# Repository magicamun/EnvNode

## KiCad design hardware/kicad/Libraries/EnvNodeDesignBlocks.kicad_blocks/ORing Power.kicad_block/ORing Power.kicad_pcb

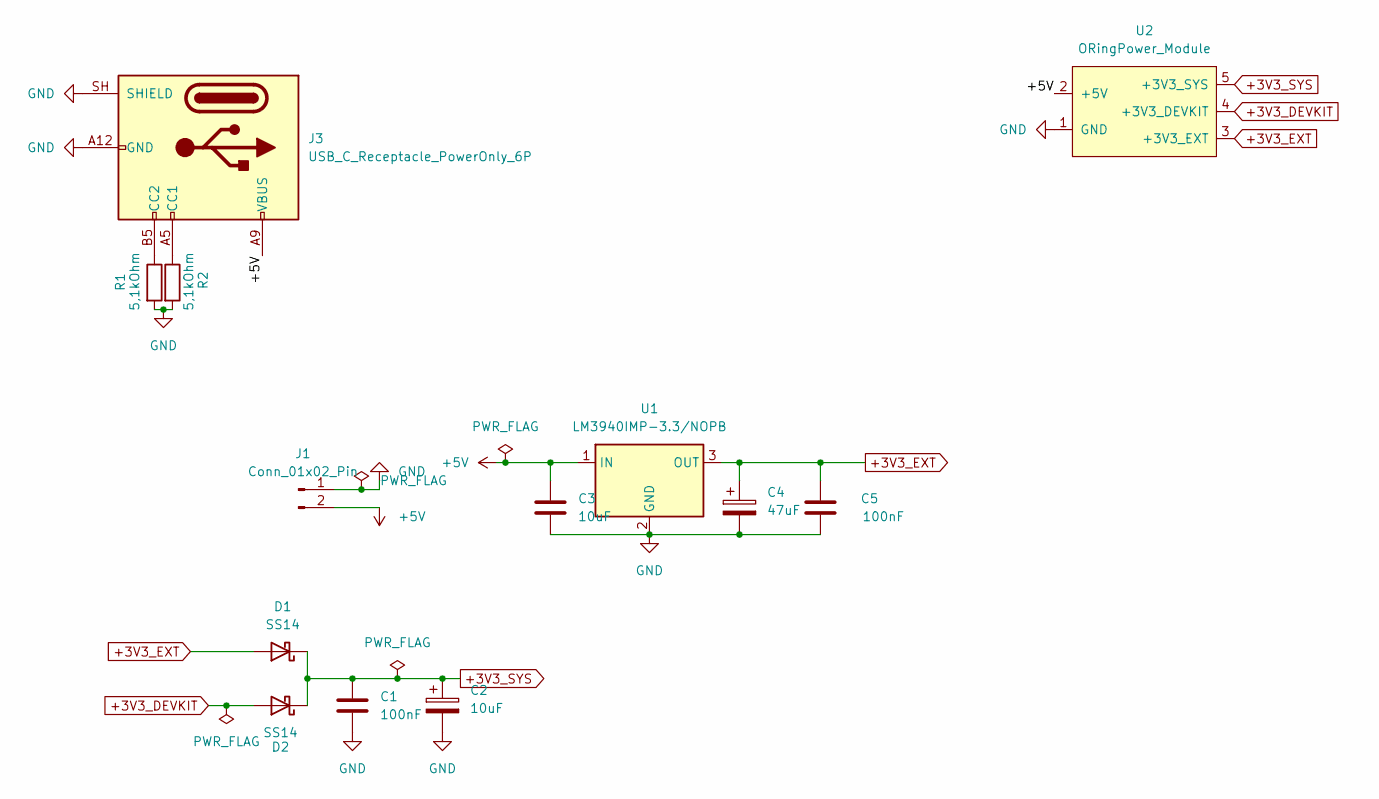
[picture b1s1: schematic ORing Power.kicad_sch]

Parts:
C1, C5: 100nF; C_1206_3216Metric_Pad1.33x1.80mm_HandSolder
C2: 10uF; CP_Elec_5x5.4
C3: 10uF; C_1206_3216Metric_Pad1.33x1.80mm_HandSolder
C4: 47uF; CP_EIA-3528-21_Kemet-B
D1, D2: SS14; D_SMA
J1: Conn_01x02_Pin; JST_PH_B2B-PH-K_1x02_P2.00mm_Vertical
J3: USB_C_Receptacle_PowerOnly_6P; USB_C_Receptacle_GCT_USB4125-xx-x-0190_6P_TopMnt_Horizontal
R1, R2: 5,1kOhm; R_1206_3216Metric_Pad1.30x1.75mm_HandSolder
U1: LM3940IMP-3.3/NOPB; SOT-223-3_TabPin2
U2: ORingPower_Module; ORingPower_Module_Castellated

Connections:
+3V3_DEVKIT: D2.2 (A), U2.4 (+3V3_DEVKIT)
+3V3_EXT: C4.1, C5.2, D1.2 (A), U1.3 (OUT), U2.3 (+3V3_EXT)
+3V3_SYS: C1.1, C2.1, D1.1 (K), D2.1 (K), U2.5 (+3V3_SYS)
+5V: C3.1, J1.2, J3.A9 (VBUS), J3.B9 (VBUS), U1.1 (IN), U2.2 (+5V)
GND: C1.2, C2.2, C3.2, C4.2, C5.1, J1.1, J3.A12 (GND), J3.B12 (GND), J3.SH (SHIELD), R1.2, R2.2, U1.2 (GND), U2.1 (GND)
unnamed: J3.A5 (CC1), R2.1
unnamed: J3.B5 (CC2), R1.1

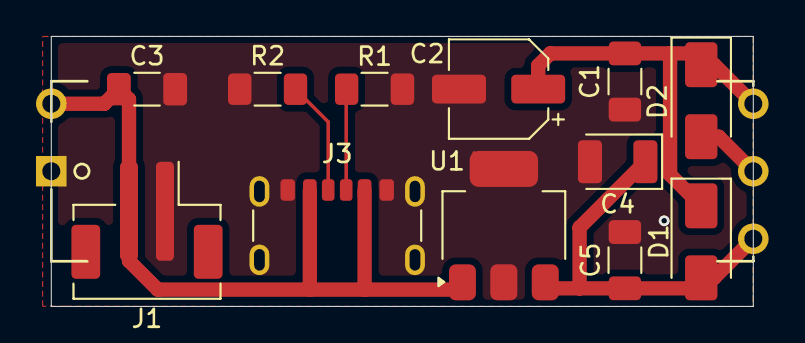
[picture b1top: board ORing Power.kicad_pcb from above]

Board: 2 copper layers, 39.0 x 15.0 mm, 13 parts (0 on the bottom side), 7 nets.

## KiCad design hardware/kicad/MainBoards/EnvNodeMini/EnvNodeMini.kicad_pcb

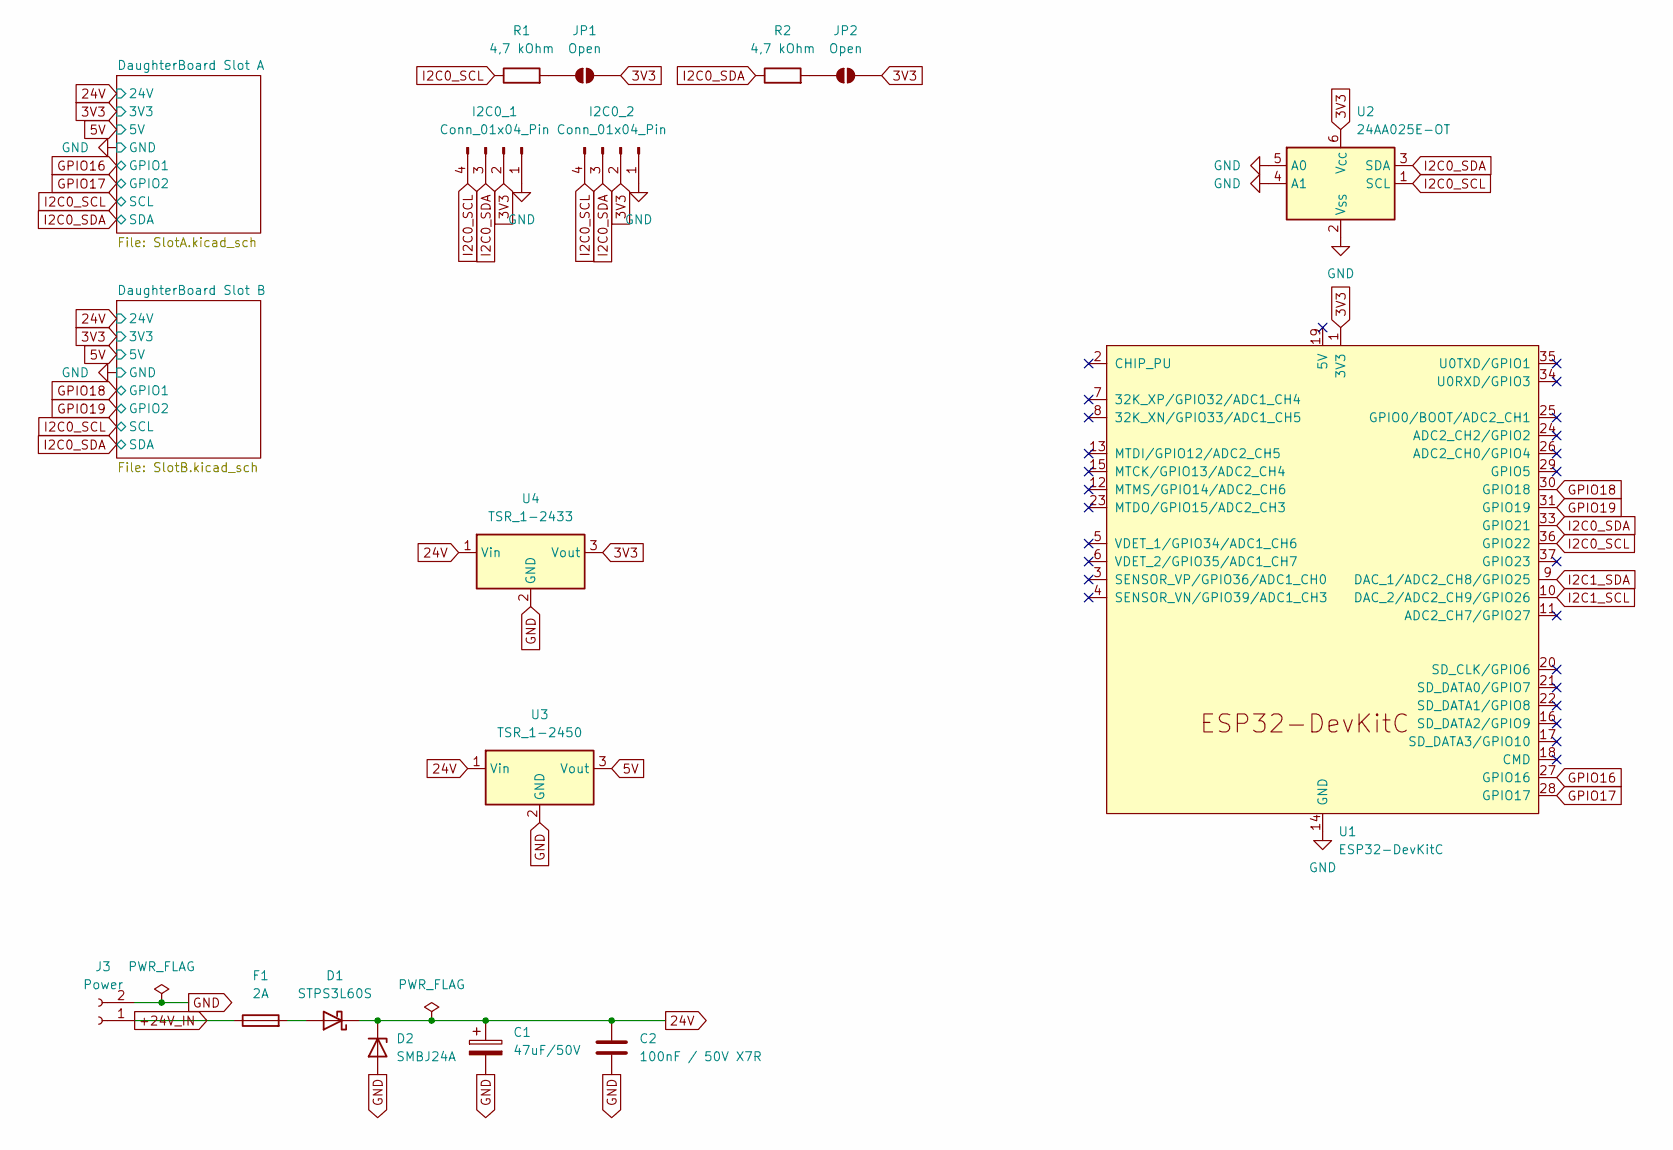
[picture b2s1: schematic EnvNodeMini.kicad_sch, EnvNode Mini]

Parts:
C1: 47uF/50V; CP_Elec_6.3x7.7
C2: 100nF / 50V X7R; C_1206_3216Metric_Pad1.33x1.80mm_HandSolder
D1: STPS3L60S; D_SMB_Handsoldering
D2: SMBJ24A; D_SMB_Handsoldering
F1: 2A; Fuse_Littelfuse-NANO2-451_453
I2C0_1, I2C0_2: Conn_01x04_Pin; JST_SH_SM04B-SRSS-TB_1x04-1MP_P1.00mm_Horizontal
J3: Power; TerminalBlock_RND_205-00001_1x02_P5.00mm_Horizontal
JP1, JP2: Open; SolderJumper-2_P1.3mm_Open_Pad1.0x1.5mm
R1, R2: 4,7 kOhm; R_1206_3216Metric_Pad1.30x1.75mm_HandSolder
U1: ESP32-DevKitC
U2: 24AA025E-OT; SOT-23-6
U3: TSR_1-2450; Converter_DCDC_TRACO_TSR-1_THT
U4: TSR_1-2433; Converter_DCDC_TRACO_TSR-1_THT

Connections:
3V3: I2C0_1.2, I2C0_2.2, JP1.2 (B), JP2.2 (B), U1.1 (3V3), U2.6 (V_{CC}), U4.3 (Vout); also elsewhere on the board
5V: U3.3 (Vout); also elsewhere on the board
24V: C1.1, C2.1, D1.1 (K), D2.1 (K), U3.1 (Vin), U4.1 (Vin); also elsewhere on the board
+24V_IN: F1.1, J3.1
GND: C1.2, C2.2, D2.2 (A), I2C0_1.1, I2C0_2.1, J3.2, U1.14 (GND), U1.32 (GND), U1.38 (GND), U2.2 (V_{SS}), U2.4 (A1), U2.5 (A0), U3.2 (GND), U4.2 (GND); also elsewhere on the board
GPIO16: U1.27 (GPIO16); also elsewhere on the board
GPIO17: U1.28 (GPIO17); also elsewhere on the board
GPIO18: U1.30 (GPIO18); also elsewhere on the board
GPIO19: U1.31 (GPIO19); also elsewhere on the board
I2C0_SCL: I2C0_1.4, I2C0_2.4, R1.1, U1.36 (GPIO22), U2.1 (SCL); also elsewhere on the board
I2C0_SDA: I2C0_1.3, I2C0_2.3, R2.1, U1.33 (GPIO21), U2.3 (SDA); also elsewhere on the board
I2C1_SCL: U1.10 (DAC_2/ADC2_CH9/GPIO26)
I2C1_SDA: U1.9 (DAC_1/ADC2_CH8/GPIO25)
unnamed: D1.2 (A), F1.2
unnamed: JP1.1 (A), R1.2
unnamed: JP2.1 (A), R2.2

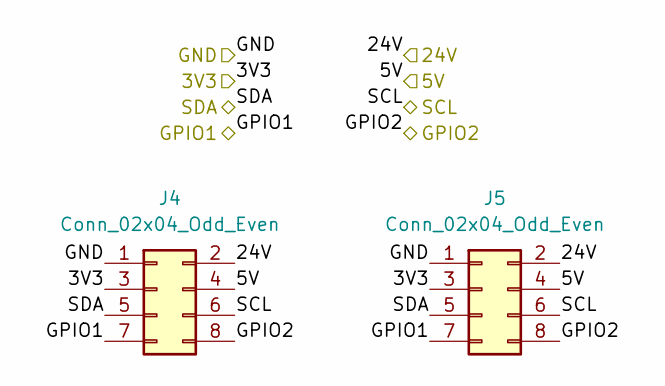
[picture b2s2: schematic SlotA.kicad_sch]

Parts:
J4, J5: Conn_02x04_Odd_Even; PinSocket_2x04_P2.54mm_Vertical

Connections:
3V3: J4.3, J5.3; also elsewhere on the board
5V: J4.4, J5.4; also elsewhere on the board
24V: J4.2, J5.2; also elsewhere on the board
GND: J4.1, J5.1; also elsewhere on the board
GPIO16: J4.7, J5.7; also elsewhere on the board
GPIO17: J4.8, J5.8; also elsewhere on the board
I2C0_SCL: J4.6, J5.6; also elsewhere on the board
I2C0_SDA: J4.5, J5.5; also elsewhere on the board

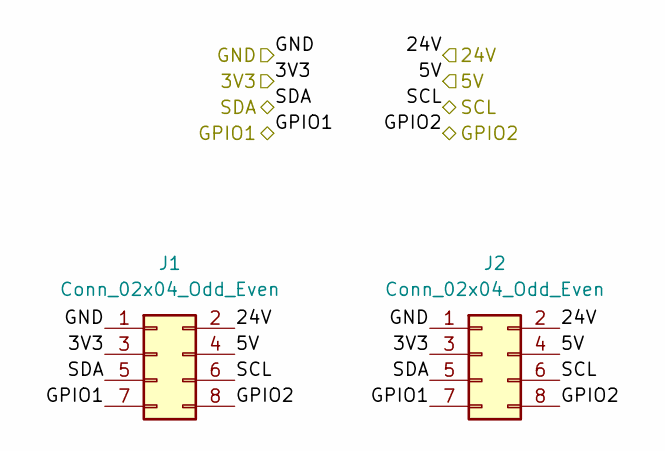
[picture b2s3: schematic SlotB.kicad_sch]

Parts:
J1, J2: Conn_02x04_Odd_Even; PinSocket_2x04_P2.54mm_Vertical

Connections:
3V3: J1.3, J2.3; also elsewhere on the board
5V: J1.4, J2.4; also elsewhere on the board
24V: J1.2, J2.2; also elsewhere on the board
GND: J1.1, J2.1; also elsewhere on the board
GPIO18: J1.7, J2.7; also elsewhere on the board
GPIO19: J1.8, J2.8; also elsewhere on the board
I2C0_SCL: J1.6, J2.6; also elsewhere on the board
I2C0_SDA: J1.5, J2.5; also elsewhere on the board

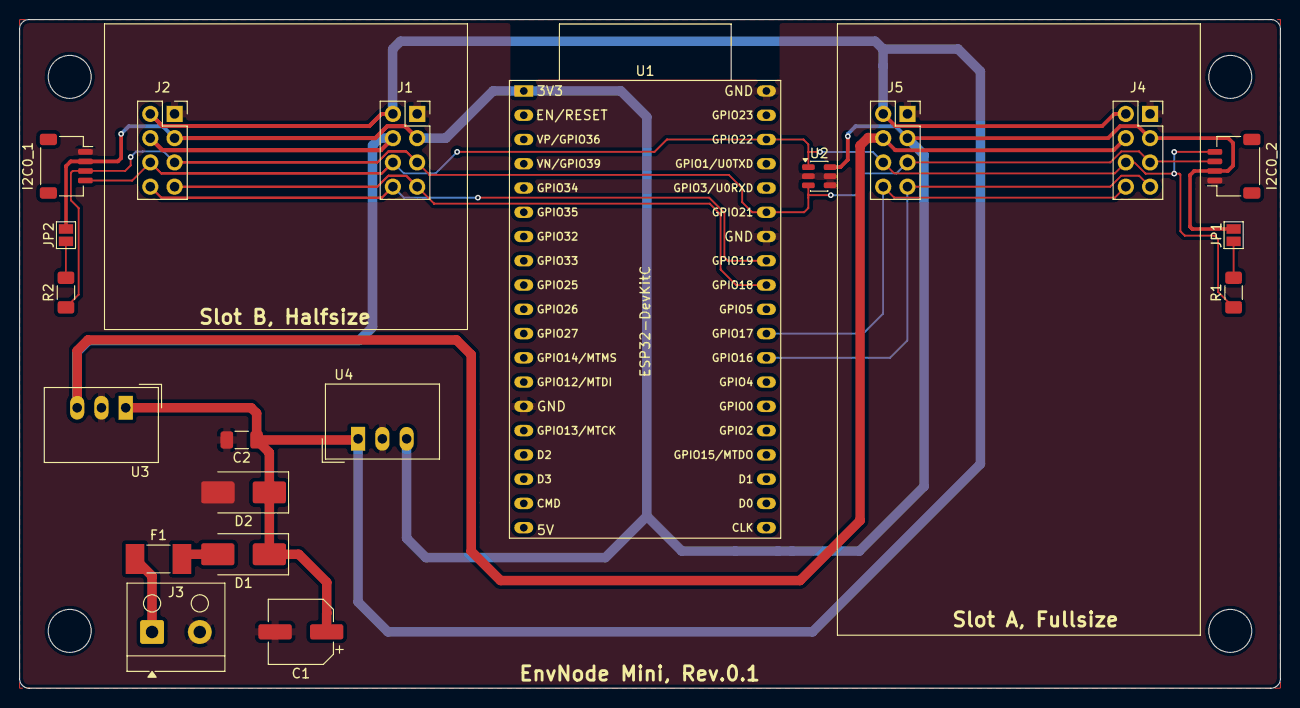
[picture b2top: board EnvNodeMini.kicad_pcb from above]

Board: 2 copper layers, 132.0 x 70.0 mm, 20 parts (0 on the bottom side), 14 nets.

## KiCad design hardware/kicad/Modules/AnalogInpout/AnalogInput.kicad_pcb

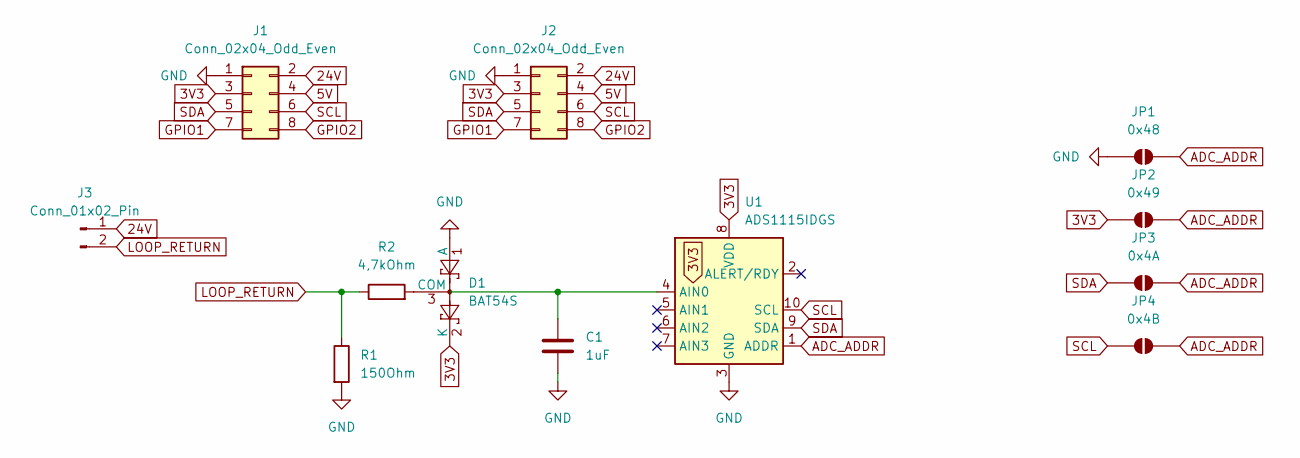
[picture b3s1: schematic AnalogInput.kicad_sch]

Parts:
C1: 1uF; C_1206_3216Metric_Pad1.33x1.80mm_HandSolder
D1: BAT54S; SOT-23
J1, J2: Conn_02x04_Odd_Even; PinSocket_2x04_P2.54mm_Vertical_Bottom
J3: Conn_01x02_Pin; PinSocket_1x02_P2.54mm_Vertical
JP1: 0x48; SolderJumper-2_P1.3mm_Open_Pad1.0x1.5mm
JP2: 0x49; SolderJumper-2_P1.3mm_Open_Pad1.0x1.5mm
JP3: 0x4A; SolderJumper-2_P1.3mm_Open_Pad1.0x1.5mm
JP4: 0x4B; SolderJumper-2_P1.3mm_Open_Pad1.0x1.5mm
R1: 150Ohm; R_1206_3216Metric_Pad1.30x1.75mm_HandSolder
R2: 4,7kOhm; R_1206_3216Metric_Pad1.30x1.75mm_HandSolder
U1: ADS1115IDGS; TSSOP-10_3x3mm_P0.5mm

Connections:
3V3: D1.2 (K), J1.3, J2.3, JP2.1 (A), U1.8 (VDD)
5V: J1.4, J2.4
24V: J1.2, J2.2, J3.1
ADC_ADDR: JP1.2 (B), JP2.2 (B), JP3.2 (B), JP4.2 (B), U1.1 (ADDR)
GND: C1.2, D1.1 (A), J1.1, J2.1, JP1.1 (A), R1.2, U1.3 (GND)
GPIO1: J1.7, J2.7
GPIO2: J1.8, J2.8
LOOP_RETURN: J3.2, R1.1, R2.1
unnamed: D1.3 (COM), R2.2
unnamed: C1.1, U1.4 (AIN0)
SCL: J1.6, J2.6, JP4.1 (A), U1.10 (SCL)
SDA: J1.5, J2.5, JP3.1 (A), U1.9 (SDA)

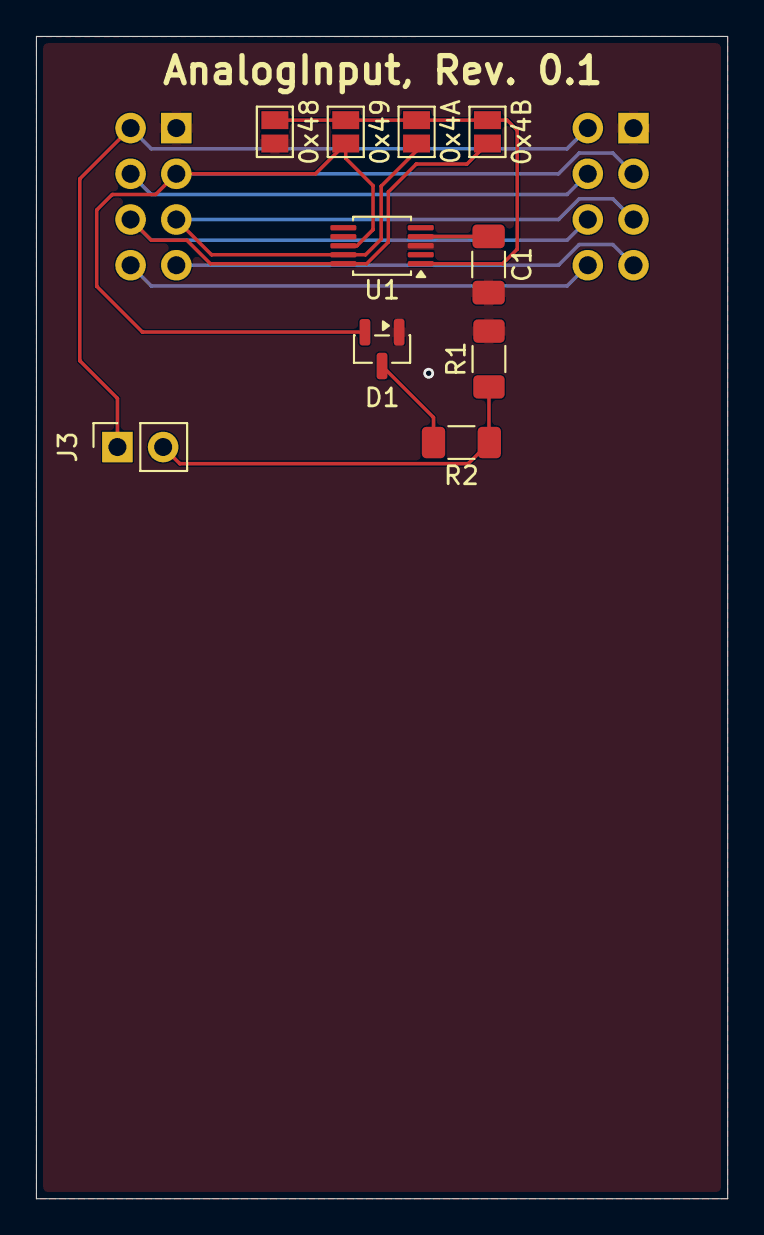
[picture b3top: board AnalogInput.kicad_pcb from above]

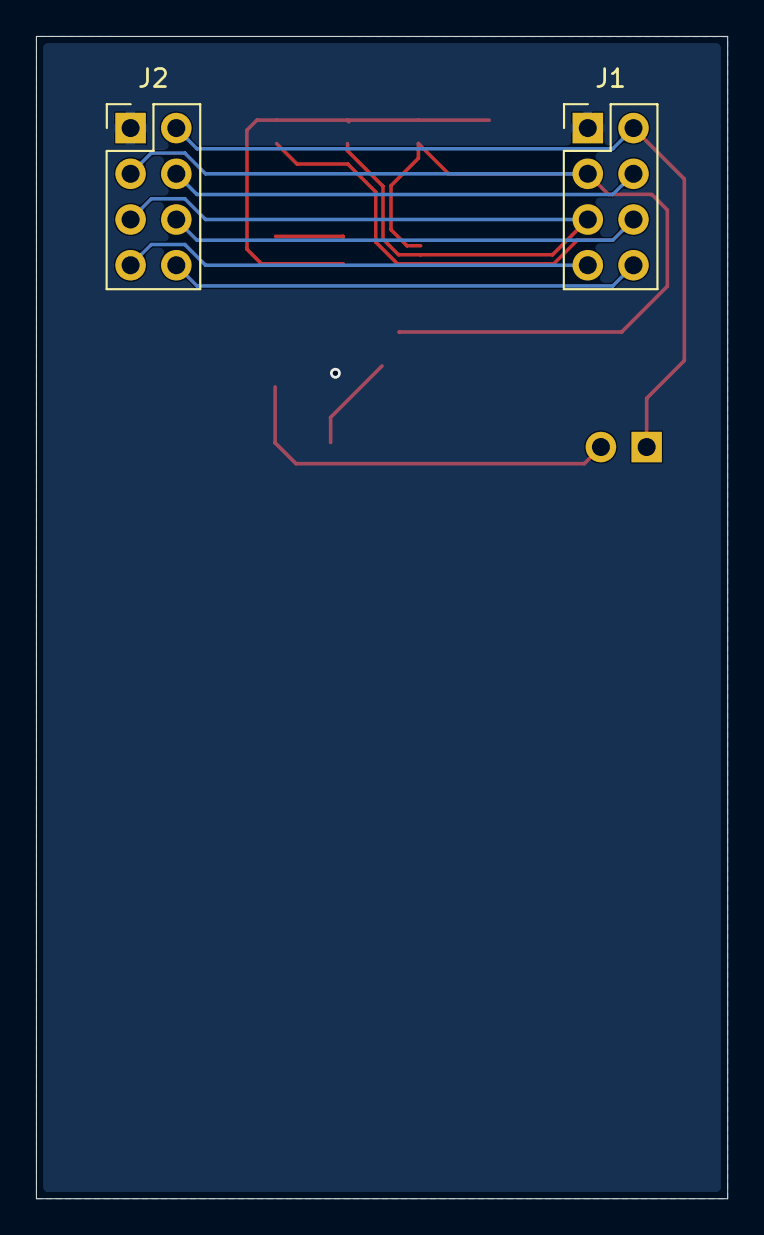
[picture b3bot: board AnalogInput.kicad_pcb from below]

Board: 2 copper layers, 38.4 x 64.6 mm, 12 parts (2 on the bottom side), 12 nets.

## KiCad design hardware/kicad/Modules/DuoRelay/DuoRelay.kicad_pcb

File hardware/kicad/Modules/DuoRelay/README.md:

# EnvNode DuoRelay

`DuoRelay` is a FullSize THT daughterboard for the EnvNode Revision 0.2 module interface. It provides two independently controlled 5 V electromechanical changeover relays.

## Project Files

- `DuoRelay.kicad_pro`
- `DuoRelay.kicad_sch`
- `DuoRelay.kicad_pcb`

## Interface Use

| Connector pin | Net | DuoRelay use |
| ---: | --- | --- |
| 1, 3 | `GND` | Control-side ground |
| 2 | `+3V3_SYS` | Not used |
| 4 | `+5V` | Relay-coil supply |
| 5–8 | I²C buses | Not used |
| 9 | `AUX_GPIO1` | Relay channel 1 control |
| 10 | `AUX_GPIO2` | Relay channel 2 control |
| 11–14 | SPI | Not used |

Each channel uses a BC817 low-side driver with a 1 kΩ base resistor, a 100 kΩ pull-down for a defined off state, and a 1N4148W flyback diode. The relays are Finder `34.51.7.005.0010` parts with 5 V coils.

## Module Identification

This revision has no module-identification EEPROM. Firmware must therefore treat the slot as unidentified and must not automatically start a DuoRelay-specific driver. The relay GPIOs are ordinary configurable `AUX_GPIO` ports until the user explicitly assigns their function.

## Mechanical Geometry

- PCB: 38.00 mm × 64.00 mm
- Connector: bottom-mounted 2 × 7 THT header
- Connector axis: centered across the board and 6.35 mm from the top edge
- Support holes: 2.7 mm for M2.5 hardware, on the centerline at 27.00 mm and 59.00 mm from the top edge

## Relay Contact Region

The relay-contact nets are routed on F.Cu with 1.0 mm tracks. The design keeps at least 8 mm between the 250 VAC contact region and all SELV copper on both layers, including GND zones, vias, pads, and traces.

The spacing and relay ratings do not by themselves certify the finished product for mains use. Terminal ratings, enclosure, touch protection, fusing, load type, pollution degree, material group, overvoltage category, manufacturing tolerances, and the applicable product standard must be assessed for the final application.

## Validation

At the time of the Revision 0.2 port:

- schematic ERC reports no errors; the remaining warnings refer only to intentionally unused connector nets;
- PCB DRC reports no violations, unconnected pads, or footprint errors; and
- connector placement, board outline, support-hole positions, power routing, relay drivers, and contact separation were checked against the source design.

ERC and DRC must be repeated after every schematic, footprint, routing, zone, or rule change.

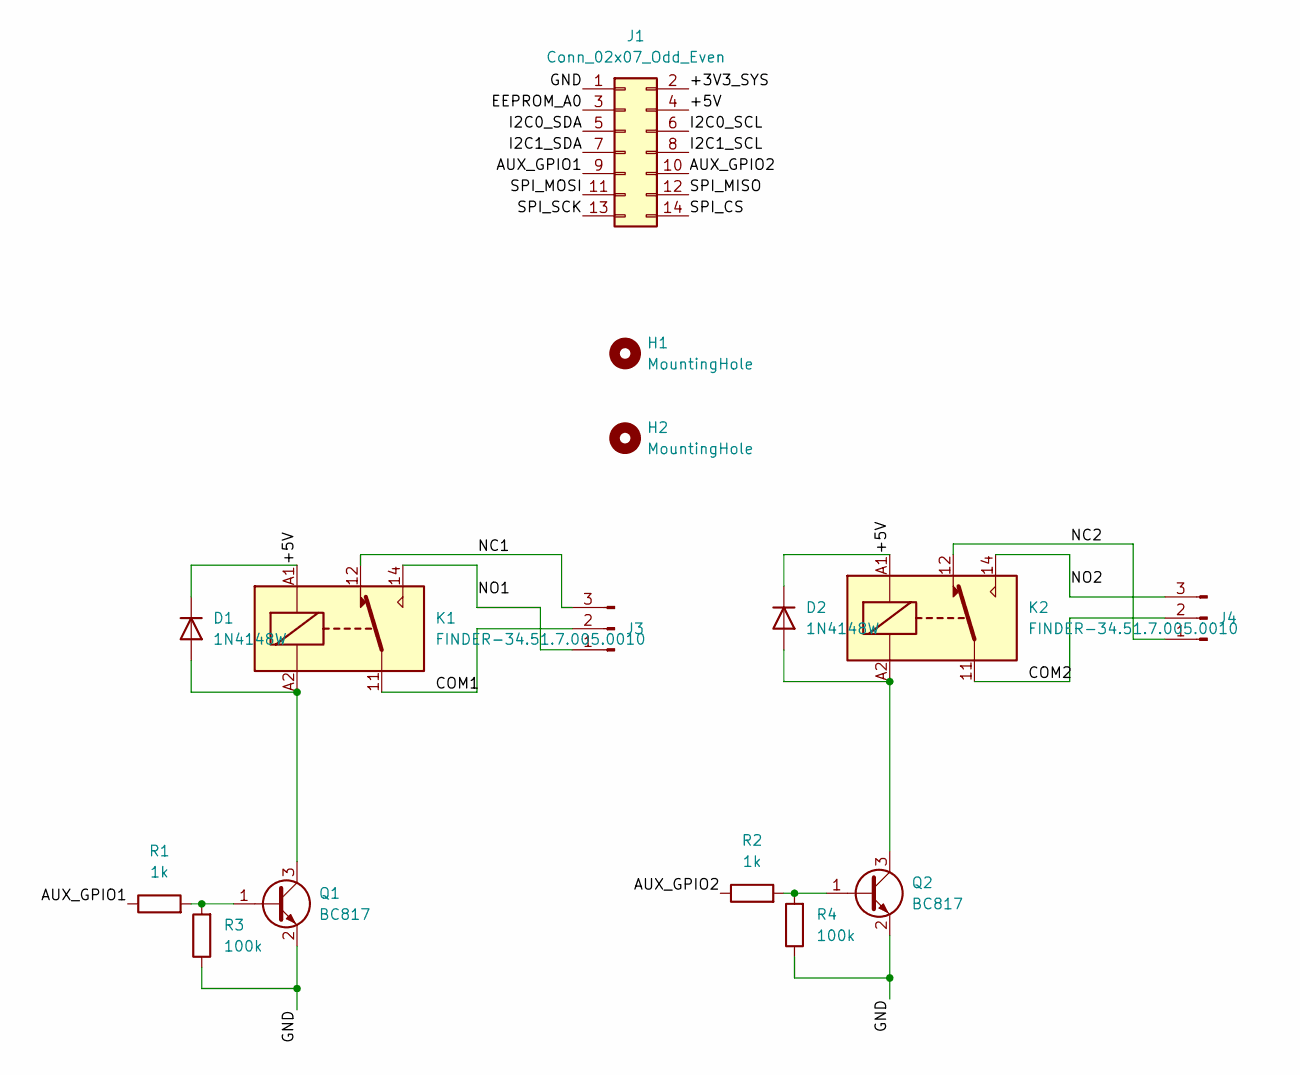
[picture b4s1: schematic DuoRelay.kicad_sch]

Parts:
D1, D2: 1N4148W; D_SOD-123
H1, H2: MountingHole; MountingHole_2.7mm_M2.5_DIN965
J1: Conn_02x07_Odd_Even; PinHeader_2x07_P2.54mm_Vertical_Bottom
J3, J4: TerminalBlock_Phoenix_MKDS-3-3-5.08_1x03_P5.08mm_Horizontal
K1, K2: FINDER-34.51.7.005.0010; Relay_SPDT_Finder_34.51_Vertical
Q1, Q2: BC817; SOT-23_Handsoldering
R1, R2: 1k; R_1206_3216Metric_Pad1.30x1.75mm_HandSolder
R3, R4: 100k; R_1206_3216Metric_Pad1.30x1.75mm_HandSolder

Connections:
/+3V3_SYS: J1.2
/+5V: D1.1 (K), D2.1 (K), J1.4, K1.A1, K2.A1
/AUX_GPIO1: J1.9, R1.1
/AUX_GPIO2: J1.10, R2.1
/COM1: J3.2, K1.11
/COM2: J4.2, K2.11
/EEPROM_A0: J1.3
/GND: J1.1, Q1.2 (E), Q2.2 (E), R3.1, R4.1
/I2C0_SCL: J1.6
/I2C0_SDA: J1.5
/I2C1_SCL: J1.8
/I2C1_SDA: J1.7
/NC1: J3.3, K1.12
/NC2: J4.1, K2.12
/NO1: J3.1, K1.14
/NO2: J4.3, K2.14
/SPI_CS: J1.14
/SPI_MISO: J1.12
/SPI_MOSI: J1.11
/SPI_SCK: J1.13
unnamed: D1.2 (A), K1.A2, Q1.3 (C)
unnamed: D2.2 (A), K2.A2, Q2.3 (C)
unnamed: Q1.1 (B), R1.2, R3.2
unnamed: Q2.1 (B), R2.2, R4.2

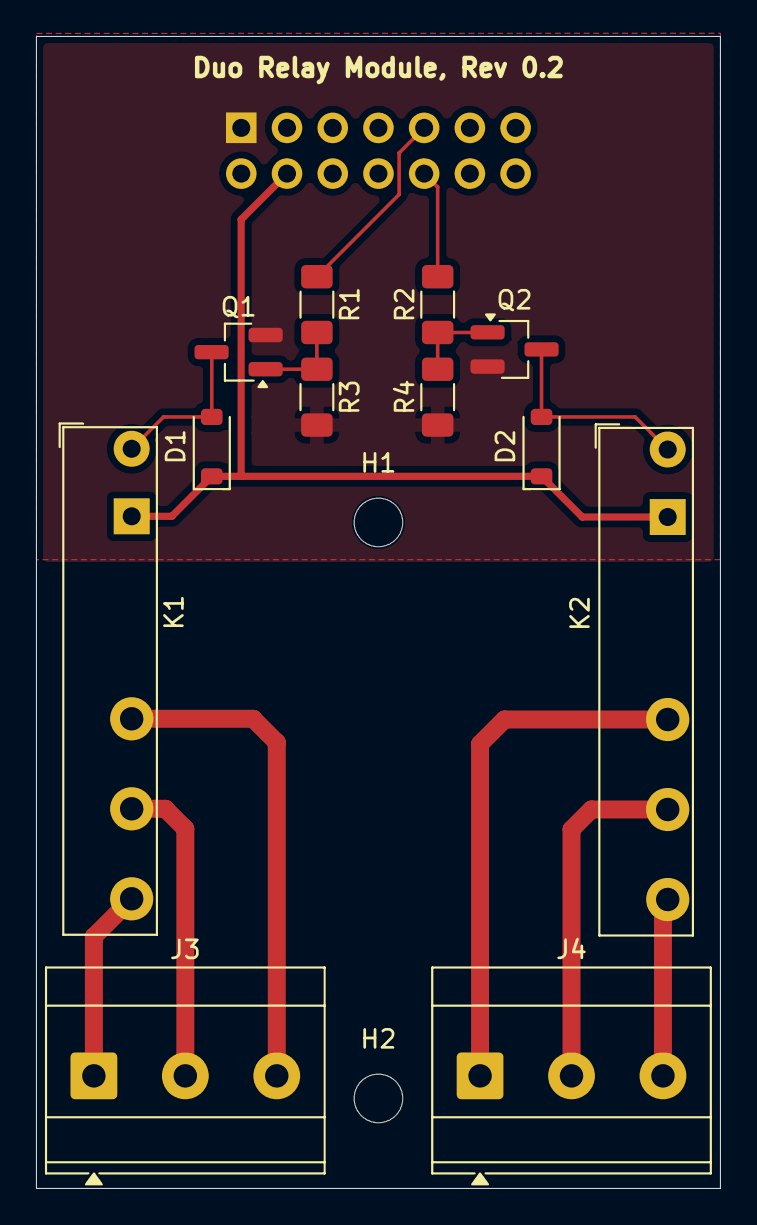
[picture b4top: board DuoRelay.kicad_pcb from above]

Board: 2 copper layers, 38.0 x 64.0 mm, 15 parts (1 on the bottom side), 14 nets.
